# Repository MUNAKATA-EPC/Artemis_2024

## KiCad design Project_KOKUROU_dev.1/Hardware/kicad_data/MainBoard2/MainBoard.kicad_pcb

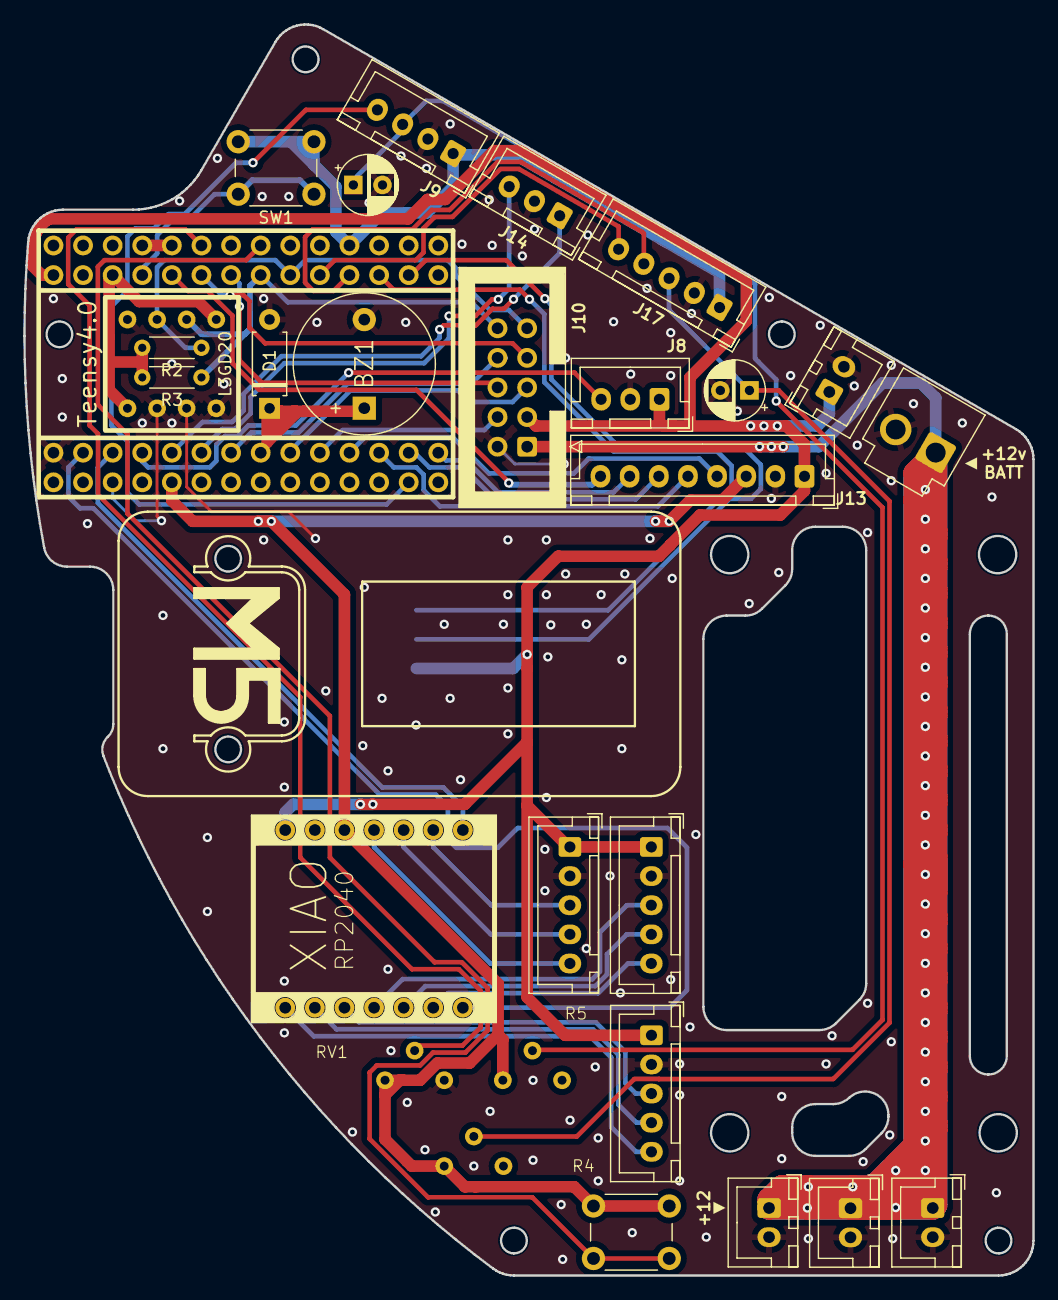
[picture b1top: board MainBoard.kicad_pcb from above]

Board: 2 copper layers, 86.6 x 107.3 mm, 29 parts (1 on the bottom side), 41 nets.

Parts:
BZ1: Buzzer; Buzzer_12x9.5RM7.6
C1, C2: C; CP_Radial_D5.0mm_P2.50mm
D1: D; D_A-405_P7.62mm_Horizontal
J1, J2, J3, J17: Conn_01x05_Socket; JST_XH_B5B-XH-A_1x05_P2.50mm_Vertical
J4, J5, J6, J12: Conn_01x02_Socket; JST_XH_B2B-XH-A_1x02_P2.50mm_Vertical
J7: Conn_01x04_Socket; JST_XH_S4B-XH-A_1x04_P2.50mm_Horizontal
J8, J14: Conn_01x03_Socket; JST_XH_B3B-XH-A_1x03_P2.50mm_Vertical
J9: Conn_01x04_Socket; JST_XH_B4B-XH-A_1x04_P2.50mm_Vertical
J10: Conn_01x10_Socket; IDC-Header_2x05_P2.54mm_Vertical
J11: Conn_01x02_Socket; JST_VH_B2P-VH-B_1x02_P3.96mm_Vertical
J13: Conn_01x08_Socket; JST_XH_B8B-XH-A_1x08_P2.50mm_Vertical
R2, R3: R; R_Axial_DIN0204_L3.6mm_D1.6mm_P5.08mm_Horizontal
R4, R5: R_Trim; 可変抵抗
RV1: R_Potentiometer_Trim_US; 可変抵抗
SW1, SW2: SW_Push; SW_PUSH_6mm_H5mm
U1: Teensy4.0; Teensy_Brakeout
U2: SeeeduinoXIAO; seeeduinoXIAO
U3: L3GD20H_Module_KiCad6.0

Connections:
+3.3V: J9.1, J13.3, J17.1, R2.2, R3.2, R4.1, R5.1, RV1.1, SW1.2, SW2.2, U1.31 (3V3), U2.12 (3V3), U3.1 (VCC), U3.8 (CS)
+5V: J1.1, J2.1, J3.1, J7.2, J8.1, J10.3, J12.1, J13.1, U1.33 (VIN), U2.14 (5V)
+12V: J4.1, J5.1, J6.1, J10.1, J11.1
BLDC_PWM: J8.3, U1.4 (2_OUT2)
BTN_EX: SW2.1, U1.37 (26_A12_MOSI1)
BTN_Left: J13.5, U1.12 (10_CS_MQSR)
BTN_Right: J13.7, U1.14 (12_MISO_MQSL)
BTN_Run: J13.6, U1.13 (11_MOSI_CTX1)
Buzzer: BZ1.1 (-), D1.1 (K), U1.8 (6_OUT1D)
CAM_RX: J10.7, U1.28 (21_A7_RX5_BCLK1)
CAM_TX: J10.6, U1.27 (20_A6_TX5_LRCLK1)
FET1_Digital: J14.1, U1.5 (3_LRCLK2)
FET2_Digital: J14.3, U1.6 (4_BCLK2)
GND: BZ1.2 (+), C1.2, C2.2, D1.2 (A), J1.2, J2.2, J3.2, J4.2, J5.2, J6.2, J7.1, J8.2, J9.2, J10.2, J11.2, J12.2, J13.2, J14.2, J17.2, RV1.3, U1.1 (GND), U2.13 (GND), U3.4 (SA0), U3.5 (GND), U3.6 (INT1), U3.7 (INT2)
IMU_RX: J7.4, U1.22 (15_A1_RX3_SPDIF_IN)
IMU_TX: J7.3, U1.21 (14_A0_TX3_SPDIF_OUT)
IND_PWM: J13.8, U1.29 (22_A8_CTX1)
IR_RX: J10.5, U1.9 (7_RX2_OUT1A)
IR_TX: J10.4, U1.10 (8_TX2_IN1)
L3GD_RST: SW1.1, U1.30 (23_A9_CRX1_MCLK1)
L3GD_SCL: J10.10, R3.1, U1.26 (19_A5_SCL0), U3.2 (SCL)
L3GD_SDA: J10.9, R2.1, U1.25 (18_A4_SDA0), U3.3 (SDA)
L3GD_Trim: RV1.2, U1.38 (27_A13_SCK1)
LINE_RX: J17.4, U1.23 (16_A2_RX4_SCL1)
LINE_TX: J17.5, U1.24 (17_A3_TX4_SDA1)
MD1_INA: J1.3, U2.3 (PA10_A2_D2)
MD1_INB: J1.4, U2.2 (PA4_A1_D1)
MD1_PWM: J1.5, U2.1 (PA02_A0_D0)
MD2_INA: J2.3, U2.4 (PA11_A3_D3)
MD2_INB: J2.4, U2.5 (PA8_A4_D4_SDA)
MD2_PWM: J2.5, U2.6 (PA9_A5_D5_SCL)
MD3_INA: J3.3, U2.9 (PA7_A8_D8_SCK)
MD3_INB: J3.4, U2.10 (PA5_A9_D9_MISO)
MD3_PWM: J3.5, U2.11 (PA6_A10_D10_MOSI)
MD_RX: U1.2 (0_RX1_CRX2_CS1), U2.7 (PB08_A6_D6_TX)
MD_TX: U1.3 (1_TX1_CTX2_MISO1), U2.8 (PB09_A7_D7_RX)
NeoPixel_PWM: J10.8, U1.7 (5_IN2)
unnamed: C2.1, J9.3, R5.2
unnamed: C1.1, J17.3, R4.2
SWT_START: J13.4, U1.11 (9_OUT1C)
Touch: J9.4, U1.41 (30_CRX3)

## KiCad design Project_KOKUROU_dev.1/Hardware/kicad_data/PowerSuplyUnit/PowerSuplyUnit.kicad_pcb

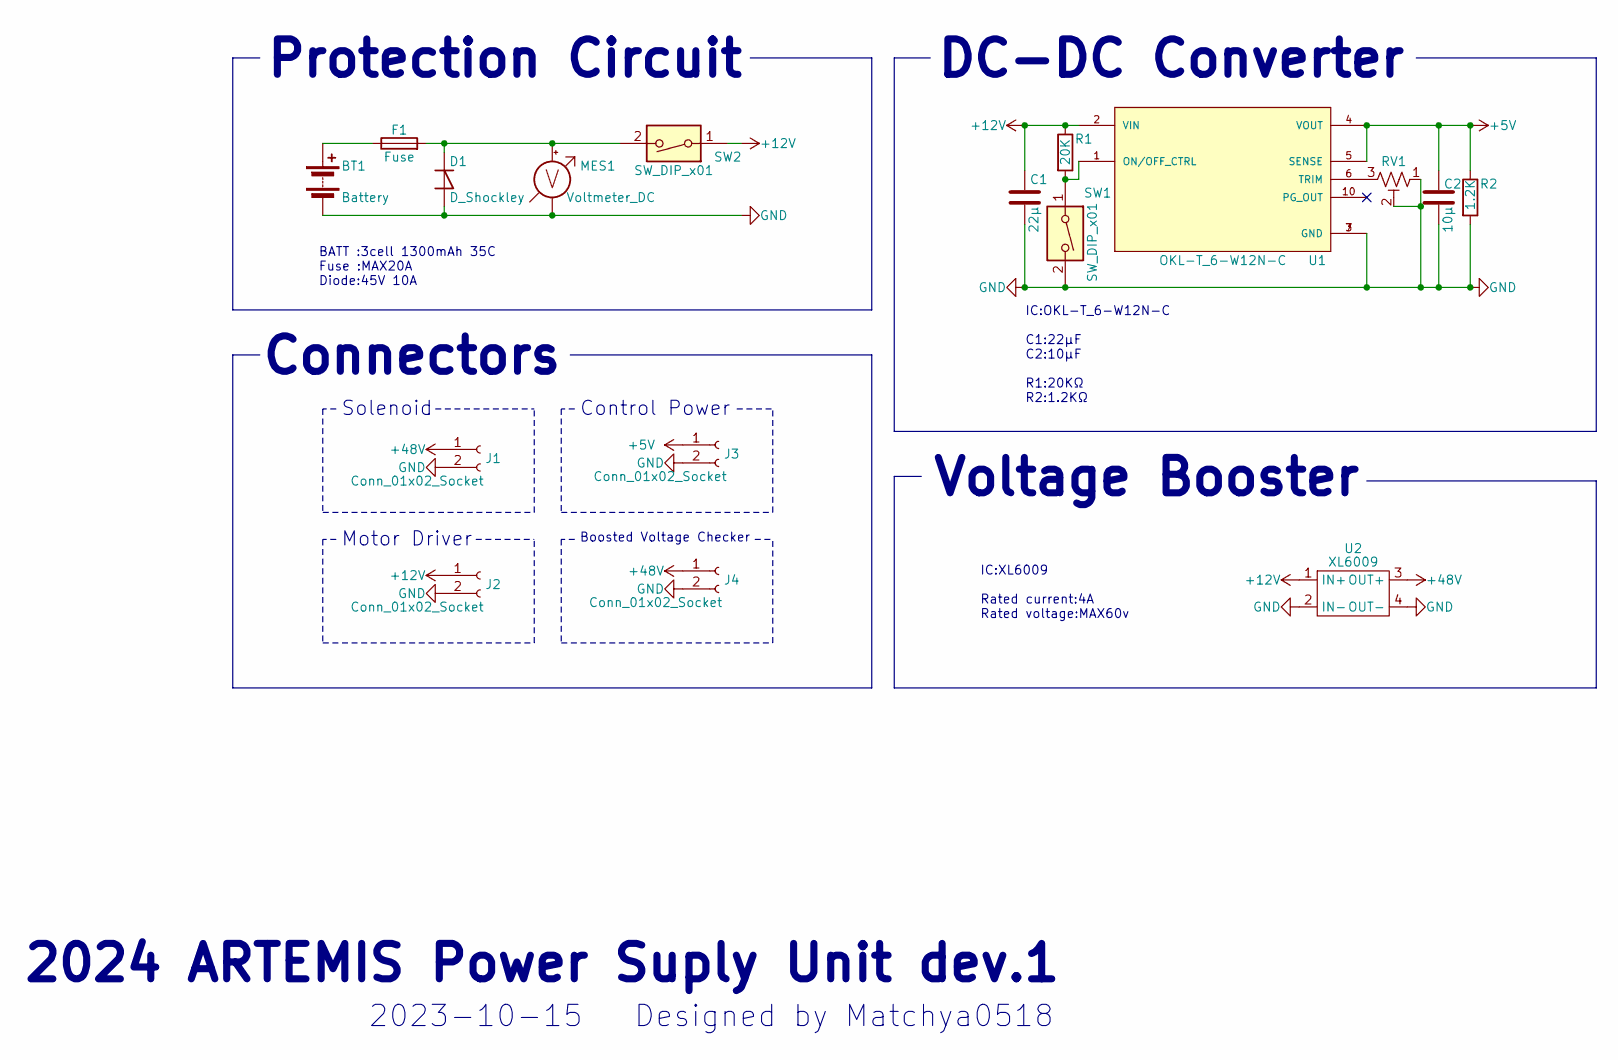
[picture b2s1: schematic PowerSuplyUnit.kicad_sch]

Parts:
BT1: Battery; JST_VH_B2P-VH_1x02_P3.96mm_Vertical
C1: 22μ; C_Disc_D4.7mm_W2.5mm_P5.00mm
C2: 10μ; C_Disc_D4.7mm_W2.5mm_P5.00mm
D1: D_Shockley; D_DO-27_P12.70mm_Horizontal
F1: Fuse; fuse_socket
J1, J3, J4: Conn_01x02_Socket; JST_XH_B2B-XH-A_1x02_P2.50mm_Vertical
J2: Conn_01x02_Socket; JST_VH_B2P-VH-B_1x02_P3.96mm_Vertical
MES1: Voltmeter_DC; voltage_counter
R1: 20K; R_Axial_DIN0204_L3.6mm_D1.6mm_P5.08mm_Horizontal
R2: 1.2K; R_Axial_DIN0204_L3.6mm_D1.6mm_P5.08mm_Horizontal
RV1: R_Potentiometer_Trim_US; Potentiometer_Bourns_3296W_Vertical
SW1: SW_DIP_x01; SW_S
SW2: SW_DIP_x01; DS-850k
U1: OKL-T_6-W12N-C; DCDC-murata-6A
U2: XL6009

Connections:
+5V: C2.1, J3.1, R2.1, U1.4 (VOUT), U1.5 (SENSE)
+12V: C1.1, J2.1, R1.1, SW2.1, U1.2 (VIN), U2.1 (IN+); also elsewhere on the board
+48V: J1.1, J4.1, U2.3 (OUT+)
GND: BT1.2 (-), C1.2, C2.2, D1.2 (A), J1.2, J2.2, J3.2, J4.2, MES1.1 (-), R2.2, RV1.1, RV1.2, SW1.2, U1.3 (GND), U1.7 (GND), U2.2 (IN-), U2.4 (OUT-); also elsewhere on the board
unnamed: BT1.1 (+), F1.1
unnamed: D1.1 (K), F1.2, MES1.2 (+), SW2.2
unnamed: R1.2, SW1.1, U1.1 (ON/OFF_CTRL)
unnamed: RV1.3, U1.6 (TRIM)

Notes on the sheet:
Control Power
BATT :3cell 1300mAh 35C Fuse :MAX20A Diode:45V 10A
Protection Circuit
Voltage Booster
IC:OKL-T_6-W12N-C C1:22μF C2:10μF R1:20KΩ R2:1.2KΩ
DC-DC Converter
IC:XL6009 Rated current:4A Rated voltage:MAX60v
Boosted Voltage Checker
Designed by Matchya0518
2024 ARTEMIS Power Suply Unit dev.1
Connectors
Solenoid
Motor Driver
2023-10-15

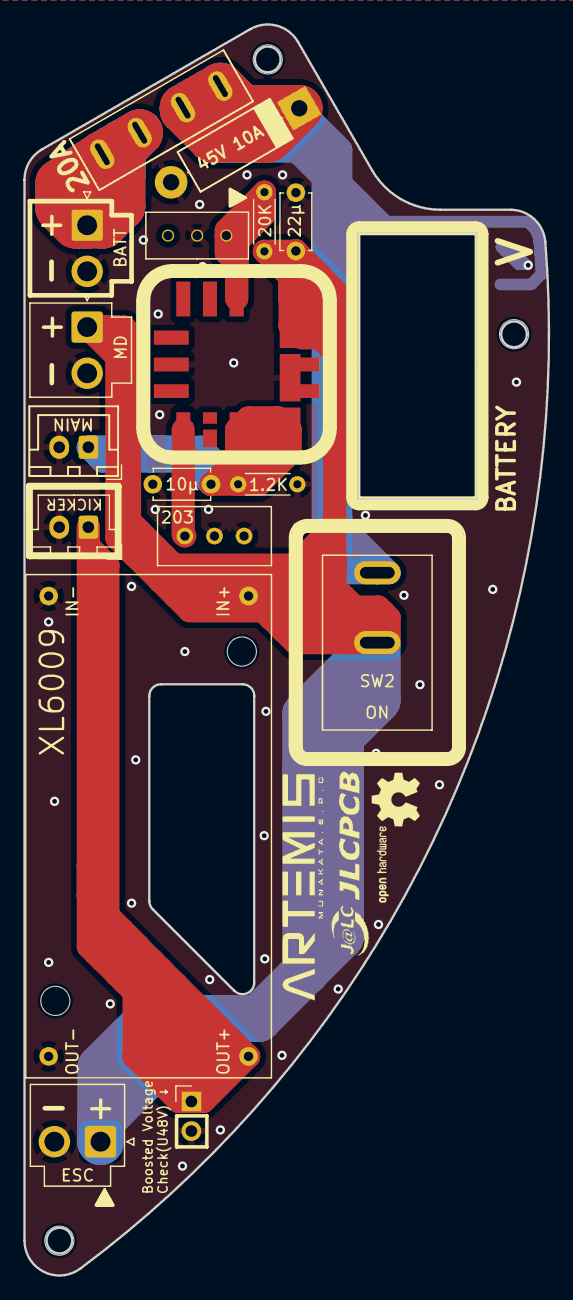
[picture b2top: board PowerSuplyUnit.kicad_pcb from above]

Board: 2 copper layers, 45.0 x 107.3 mm, 18 parts (0 on the bottom side), 8 nets.

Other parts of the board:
J2#2: Conn_01x02_Socket; JST_VH_B2P-VH-B_1x02_P3.96mm_Vertical

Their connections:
+12V: J2#2.1; also elsewhere on the board
GND: J2#2.2; also elsewhere on the board

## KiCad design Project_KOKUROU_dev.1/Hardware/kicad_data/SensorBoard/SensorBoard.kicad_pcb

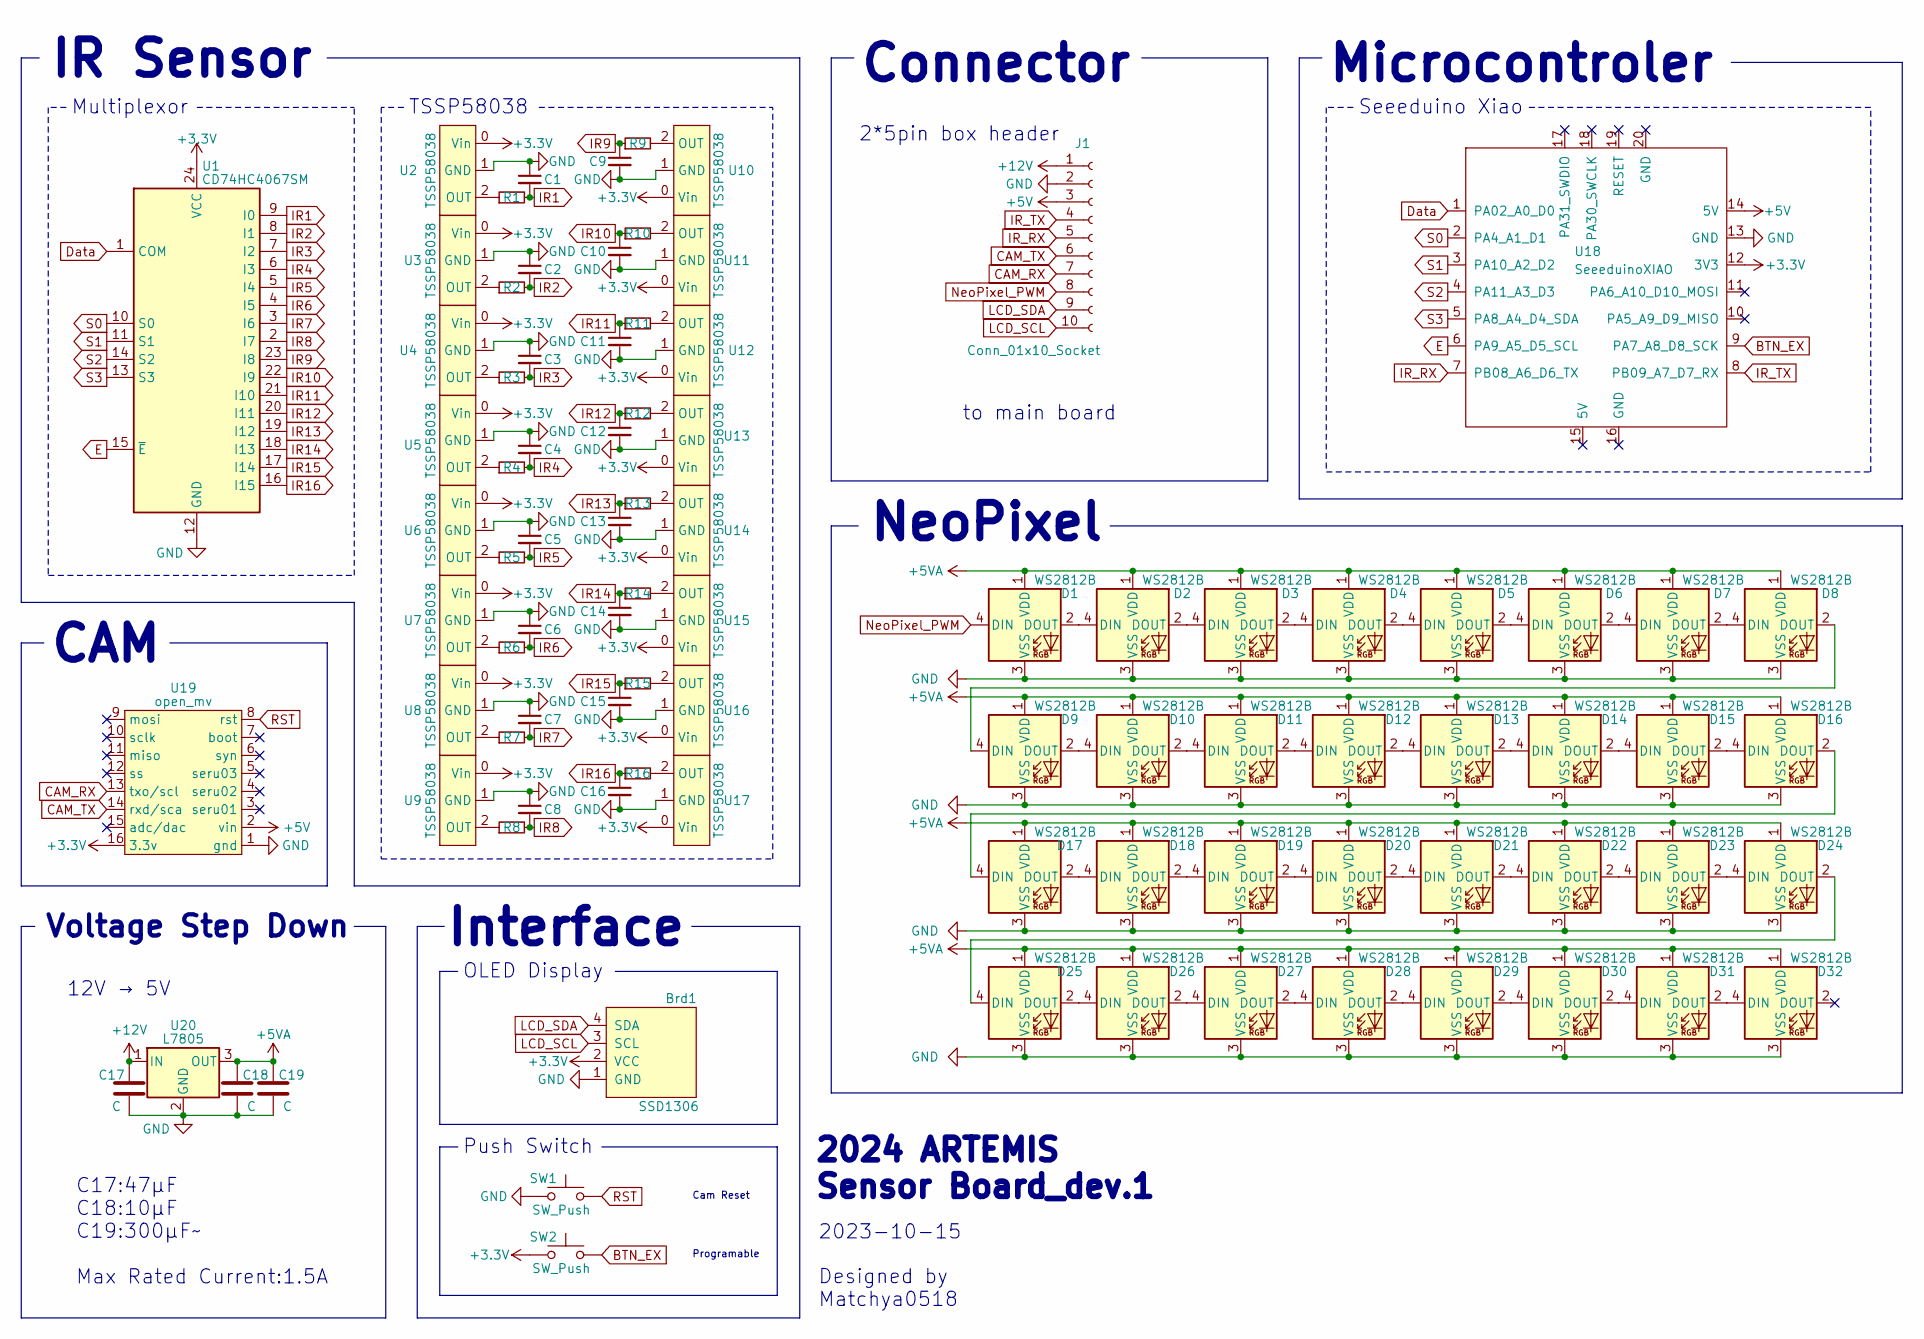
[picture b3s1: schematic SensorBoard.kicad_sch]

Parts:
Brd1: SSD1306; 128x64OLED
C1, C2, C3, C4, C5, C6, C7, C8, C9, C10, C11, C12, C13, C14, C15, C16: C_Small; C_0402_1005Metric
C17, C19: C; CP_Elec_5x5.4
C18: C; C_0402_1005Metric
D1, D2, D3, D4, D5, D6, D7, D8, D9, D10, D11, D12, D13, D14, D15, D16, D17, D18, D19, D20, D21, D22, D23, D24, D25, D26, D27, D28, D29, D30, D31, D32: WS2812B; LED_WS2812B-Mini_3.5x3.5mm
J1: Conn_01x10_Socket; IDC-Header_2x05_P2.54mm_Vertical
R1, R2, R3, R4, R5, R6, R7, R8, R9, R10, R11, R12, R13, R14, R15, R16: R_Small; C_0402_1005Metric
SW1, SW2: SW_Push; SW_PUSH_6mm_H5mm
U1: CD74HC4067SM; SSOP-24_5.3x8.2mm_P0.65mm
U2, U3, U4, U5, U6, U7, U8, U9, U10, U11, U12, U13, U14, U15, U16, U17: TSSP58038
U18: SeeeduinoXIAO; seeeduinoXIAO
U19: open_mv; OpenMV
U20: L7805; 3端子レギュレータ

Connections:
+3.3V: Brd1.2 (VCC), SW2.1, U1.24 (VCC), U2.0 (Vin), U3.0 (Vin), U4.0 (Vin), U5.0 (Vin), U6.0 (Vin), U7.0 (Vin), U8.0 (Vin), U9.0 (Vin), U10.0 (Vin), U11.0 (Vin), U12.0 (Vin), U13.0 (Vin), U14.0 (Vin), U15.0 (Vin), U16.0 (Vin), U17.0 (Vin), U18.12 (3V3), U19.16 (3.3v)
+5V: J1.3, U18.14 (5V), U19.2 (vin)
+5VA: C18.1, C19.1, D1.1 (VDD), D2.1 (VDD), D3.1 (VDD), D4.1 (VDD), D5.1 (VDD), D6.1 (VDD), D7.1 (VDD), D8.1 (VDD), D9.1 (VDD), D10.1 (VDD), D11.1 (VDD), D12.1 (VDD), D13.1 (VDD), D14.1 (VDD), D15.1 (VDD), D16.1 (VDD), D17.1 (VDD), D18.1 (VDD), D19.1 (VDD), D20.1 (VDD), D21.1 (VDD), D22.1 (VDD), D23.1 (VDD), D24.1 (VDD), D25.1 (VDD), D26.1 (VDD), D27.1 (VDD), D28.1 (VDD), D29.1 (VDD), D30.1 (VDD), D31.1 (VDD), D32.1 (VDD), U20.3 (OUT)
+12V: C17.1, J1.1, U20.1 (IN)
BTN_EX: SW2.2, U18.9 (PA7_A8_D8_SCK)
CAM_RX: J1.7, U19.13 (txo/scl)
CAM_TX: J1.6, U19.14 (rxd/sca)
Data: U1.1 (COM), U18.1 (PA02_A0_D0)
E: U1.15 (~E), U18.6 (PA9_A5_D5_SCL)
GND: Brd1.1 (GND), C1.1, C2.1, C3.1, C4.1, C5.1, C6.1, C7.1, C8.1, C9.2, C10.2, C11.2, C12.2, C13.2, C14.2, C15.2, C16.2, C17.2, C18.2, C19.2, D1.3 (VSS), D2.3 (VSS), D3.3 (VSS), D4.3 (VSS), D5.3 (VSS), D6.3 (VSS), D7.3 (VSS), D8.3 (VSS), D9.3 (VSS), D10.3 (VSS), D11.3 (VSS), D12.3 (VSS), D13.3 (VSS), D14.3 (VSS), D15.3 (VSS), D16.3 (VSS), D17.3 (VSS), D18.3 (VSS), D19.3 (VSS), D20.3 (VSS), D21.3 (VSS), D22.3 (VSS), D23.3 (VSS), D24.3 (VSS), D25.3 (VSS), D26.3 (VSS), D27.3 (VSS), D28.3 (VSS), D29.3 (VSS), D30.3 (VSS), D31.3 (VSS), D32.3 (VSS), J1.2, SW1.1, U1.12 (GND), U2.1 (GND), U3.1 (GND), U4.1 (GND), U5.1 (GND), U6.1 (GND), U7.1 (GND), U8.1 (GND), U9.1 (GND), U10.1 (GND), U11.1 (GND), U12.1 (GND), U13.1 (GND), U14.1 (GND), U15.1 (GND), U16.1 (GND), U17.1 (GND), U18.13 (GND), U19.1 (gnd), U20.2 (GND)
IR1: C1.2, R1.2, U1.9 (I0)
IR2: C2.2, R2.2, U1.8 (I1)
IR3: C3.2, R3.2, U1.7 (I2)
IR4: C4.2, R4.2, U1.6 (I3)
IR5: C5.2, R5.2, U1.5 (I4)
IR6: C6.2, R6.2, U1.4 (I5)
IR7: C7.2, R7.2, U1.3 (I6)
IR8: C8.2, R8.2, U1.2 (I7)
IR9: C9.1, R9.1, U1.23 (I8)
IR10: C10.1, R10.1, U1.22 (I9)
IR11: C11.1, R11.1, U1.21 (I10)
IR12: C12.1, R12.1, U1.20 (I11)
IR13: C13.1, R13.1, U1.19 (I12)
IR14: C14.1, R14.1, U1.18 (I13)
IR15: C15.1, R15.1, U1.17 (I14)
IR16: C16.1, R16.1, U1.16 (I15)
IR_RX: J1.5, U18.7 (PB08_A6_D6_TX)
IR_TX: J1.4, U18.8 (PB09_A7_D7_RX)
LCD_SCL: Brd1.3 (SCL), J1.10
LCD_SDA: Brd1.4 (SDA), J1.9
NeoPixel_PWM: D1.4 (DIN), J1.8
unnamed: D1.2 (DOUT), D2.4 (DIN)
unnamed: D2.2 (DOUT), D3.4 (DIN)
unnamed: D3.2 (DOUT), D4.4 (DIN)
unnamed: D4.2 (DOUT), D5.4 (DIN)
unnamed: D5.2 (DOUT), D6.4 (DIN)
unnamed: D6.2 (DOUT), D7.4 (DIN)
unnamed: D7.2 (DOUT), D8.4 (DIN)
unnamed: D8.2 (DOUT), D9.4 (DIN)
unnamed: D9.2 (DOUT), D10.4 (DIN)
unnamed: D10.2 (DOUT), D11.4 (DIN)
unnamed: D11.2 (DOUT), D12.4 (DIN)
unnamed: D12.2 (DOUT), D13.4 (DIN)
unnamed: D13.2 (DOUT), D14.4 (DIN)
unnamed: D14.2 (DOUT), D15.4 (DIN)
unnamed: D15.2 (DOUT), D16.4 (DIN)
unnamed: D16.2 (DOUT), D17.4 (DIN)
unnamed: D17.2 (DOUT), D18.4 (DIN)
unnamed: D18.2 (DOUT), D19.4 (DIN)
unnamed: D19.2 (DOUT), D20.4 (DIN)
unnamed: D20.2 (DOUT), D21.4 (DIN)
unnamed: D21.2 (DOUT), D22.4 (DIN)
unnamed: D22.2 (DOUT), D23.4 (DIN)
unnamed: D23.2 (DOUT), D24.4 (DIN)
unnamed: D24.2 (DOUT), D25.4 (DIN)
unnamed: D25.2 (DOUT), D26.4 (DIN)
unnamed: D26.2 (DOUT), D27.4 (DIN)
unnamed: D27.2 (DOUT), D28.4 (DIN)
unnamed: D28.2 (DOUT), D29.4 (DIN)
unnamed: D29.2 (DOUT), D30.4 (DIN)
unnamed: D30.2 (DOUT), D31.4 (DIN)
unnamed: D31.2 (DOUT), D32.4 (DIN)
unnamed: R1.1, U2.2 (OUT)
unnamed: R2.1, U3.2 (OUT)
unnamed: R3.1, U4.2 (OUT)
unnamed: R4.1, U5.2 (OUT)
unnamed: R5.1, U6.2 (OUT)
unnamed: R6.1, U7.2 (OUT)
unnamed: R7.1, U8.2 (OUT)
unnamed: R8.1, U9.2 (OUT)
unnamed: R9.2, U10.2 (OUT)
unnamed: R10.2, U11.2 (OUT)
unnamed: R11.2, U12.2 (OUT)
unnamed: R12.2, U13.2 (OUT)
unnamed: R13.2, U14.2 (OUT)
unnamed: R14.2, U15.2 (OUT)
unnamed: R15.2, U16.2 (OUT)
unnamed: R16.2, U17.2 (OUT)
RST: SW1.2, U19.8 (rst)
S0: U1.10 (S0), U18.2 (PA4_A1_D1)
S1: U1.11 (S1), U18.3 (PA10_A2_D2)
S2: U1.14 (S2), U18.4 (PA11_A3_D3)
S3: U1.13 (S3), U18.5 (PA8_A4_D4_SDA)

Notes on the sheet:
Seeeduino Xiao
IR Sensor
2024 ARTEMIS Sensor Board_dev.1
Push Switch
TSSP58038
to main board
Programable
Voltage Step Down
C17:47μF C18:10μF C19:300μF~ Max Rated Current:1.5A
CAM
12V → 5V
Designed by Matchya0518
2023-10-15
Microcontroler
NeoPixel
Interface
Cam Reset
Multiplexor
OLED Display
Connector
2*5pin box header

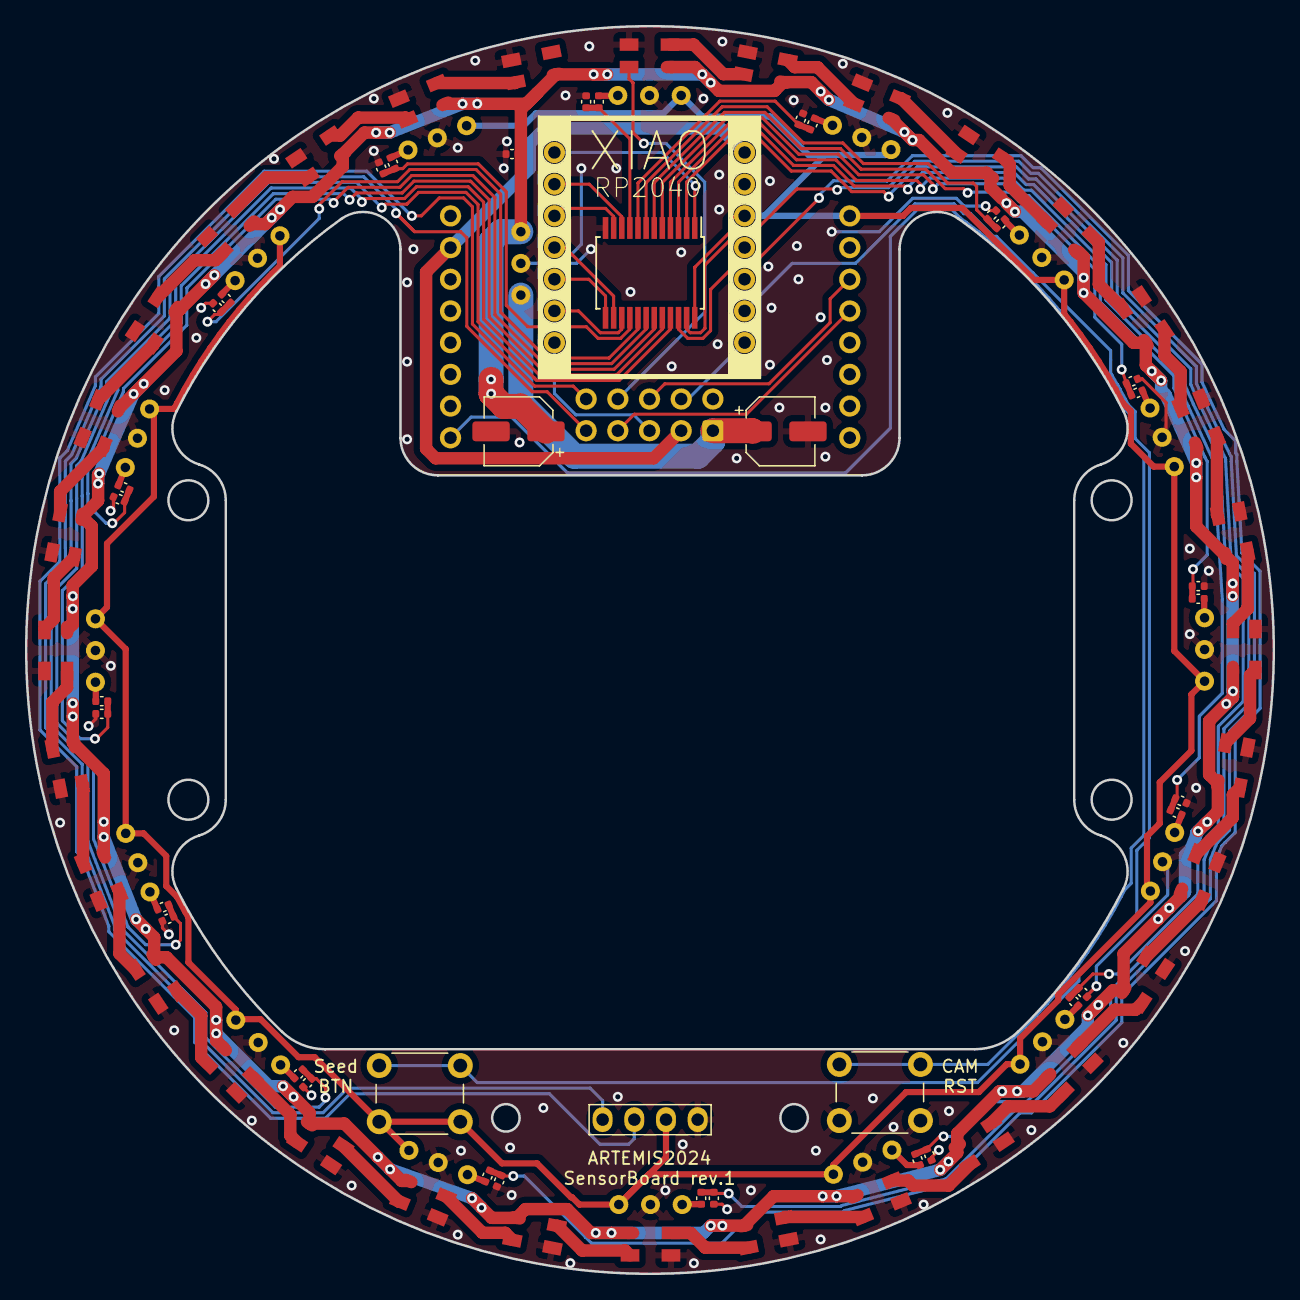
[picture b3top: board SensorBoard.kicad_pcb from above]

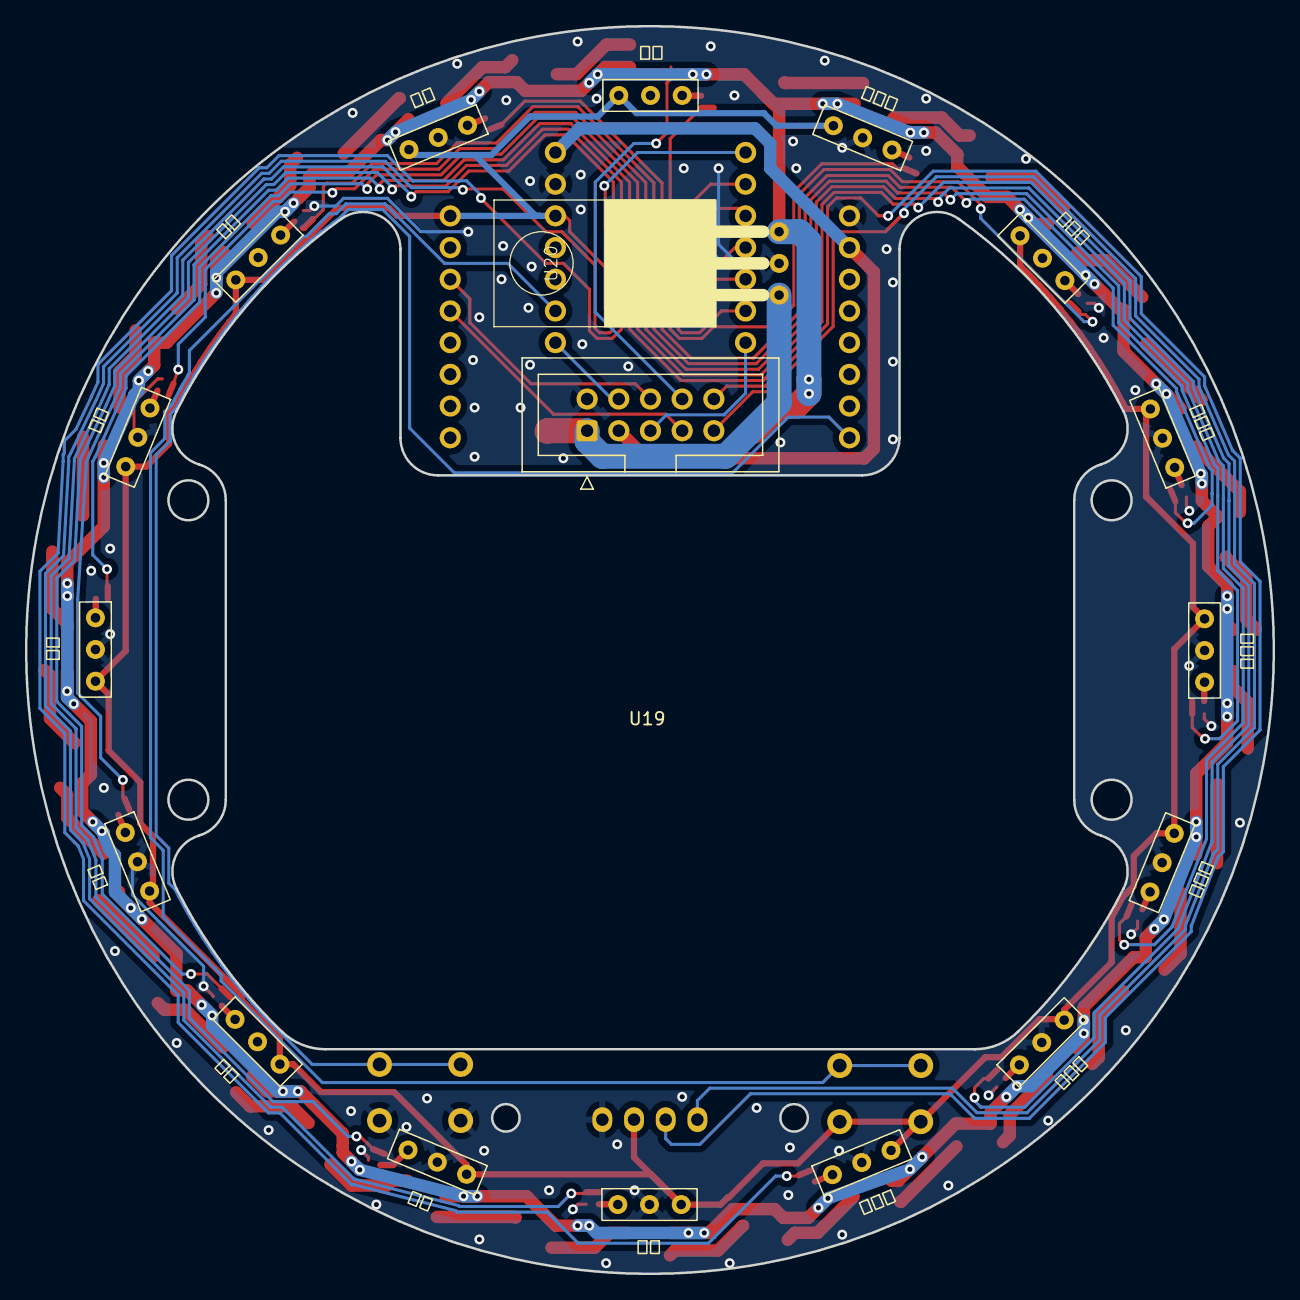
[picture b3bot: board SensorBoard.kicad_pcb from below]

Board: 2 copper layers, 100.0 x 100.0 mm, 91 parts (19 on the bottom side), 83 nets.

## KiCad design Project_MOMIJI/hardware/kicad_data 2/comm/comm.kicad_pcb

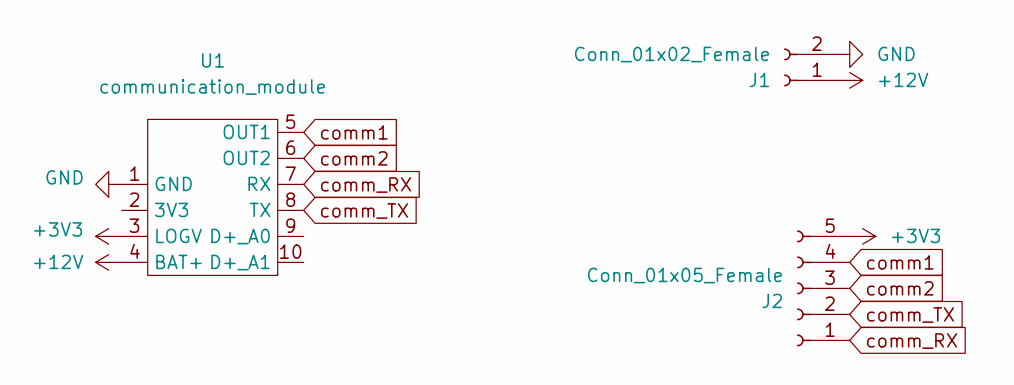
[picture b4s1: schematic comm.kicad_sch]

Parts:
J1: Conn_01x02_Female; JST_XH_S2B-XH-A_1x02_P2.50mm_Horizontal
J2: Conn_01x05_Female; JST_XH_S5B-XH-A_1x05_P2.50mm_Horizontal
U1: communication_module; comm

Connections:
+3V3: J2.5, U1.3 (LOGV)
+12V: J1.1, U1.4 (BAT+)
GND: J1.2, U1.1 (GND)
comm1: J2.4, U1.5 (OUT1)
comm2: J2.3, U1.6 (OUT2)
comm_RX: J2.1, U1.7 (RX)
comm_TX: J2.2, U1.8 (TX)

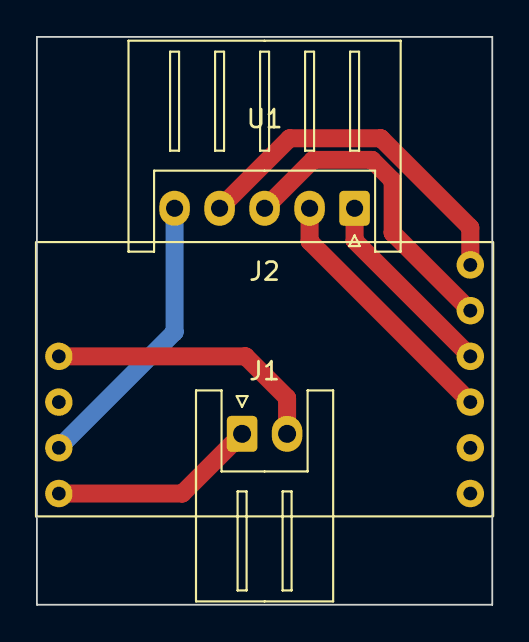
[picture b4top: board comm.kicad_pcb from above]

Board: 2 copper layers, 25.3 x 31.5 mm, 3 parts (0 on the bottom side), 7 nets.

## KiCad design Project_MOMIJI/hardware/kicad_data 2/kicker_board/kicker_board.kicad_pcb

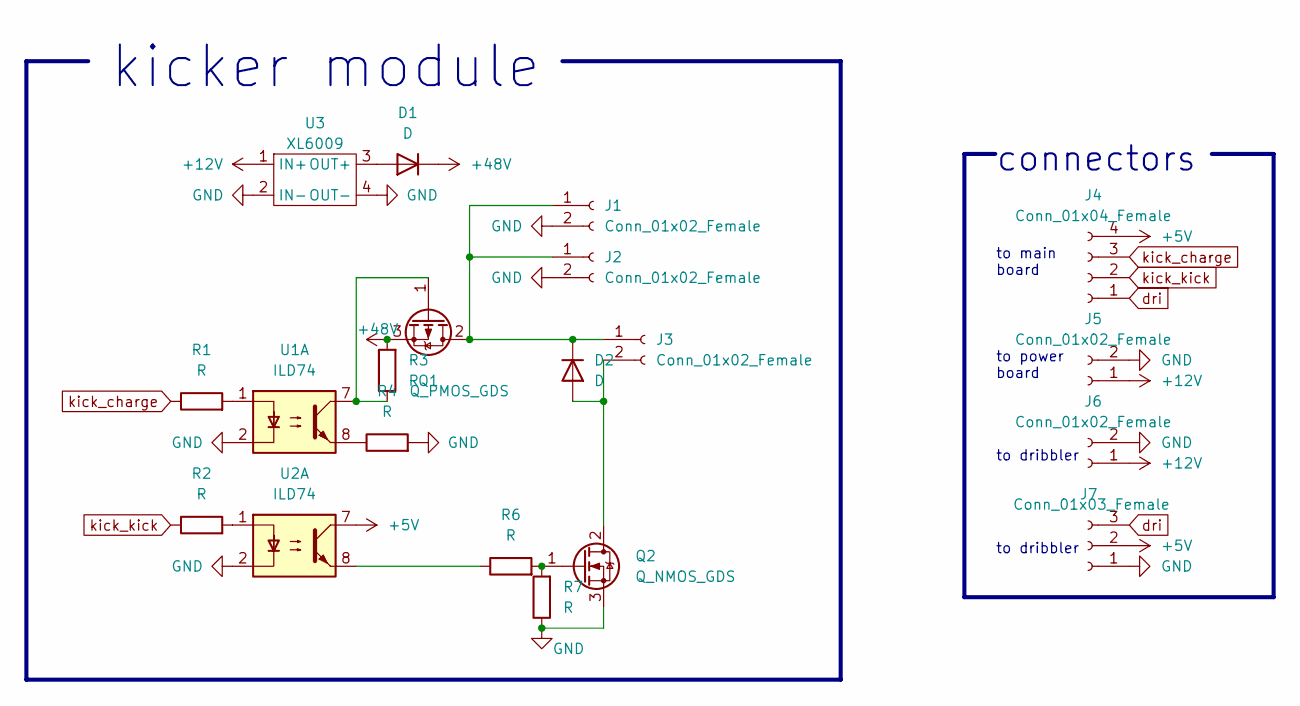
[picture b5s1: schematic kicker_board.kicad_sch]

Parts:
D1, D2: D; D_5W_P12.70mm_Horizontal
J1, J2, J3, J5, J6: Conn_01x02_Female; JST_XH_B2B-XH-A_1x02_P2.50mm_Vertical
J4: Conn_01x04_Female; JST_XH_B4B-XH-A_1x04_P2.50mm_Vertical
J7: Conn_01x03_Female; JST_XH_B3B-XH-A_1x03_P2.50mm_Vertical
Q1: Q_PMOS_GDS; Pch MOSFET
Q2: Q_NMOS_GDS; Pch MOSFET
R1, R2, R3, R4, R6, R7: R; R_Axial_DIN0207_L6.3mm_D2.5mm_P7.62mm_Horizontal
U1, U2: ILD74; フォトカプラー
U3: XL6009

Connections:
+5V: J4.4, J7.2, U2.7
+12V: J5.1, J6.1, U3.1 (IN+)
+48V: D1.1 (K), Q1.3 (S), R3.2
GND: J1.2, J2.2, J5.2, J6.2, J7.1, Q2.3 (S), R4.2, R7.1, U1.2, U2.2, U3.2 (IN-), U3.4 (OUT-)
unnamed: D1.2 (A), U3.3 (OUT+)
unnamed: D2.1 (K), J1.1, J2.1, J3.1, Q1.2 (D)
unnamed: D2.2 (A), J3.2, Q2.2 (D)
unnamed: Q1.1 (G), R3.1, U1.7
unnamed: Q2.1 (G), R6.2, R7.2
unnamed: R1.2, U1.1
unnamed: R2.2, U2.1
unnamed: R4.1, U1.8
unnamed: R6.1, U2.8
dri: J4.1, J7.3
kick_charge: J4.3, R1.1
kick_kick: J4.2, R2.1

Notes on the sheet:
to dribbler
kicker module
to main board
connectors
to power board

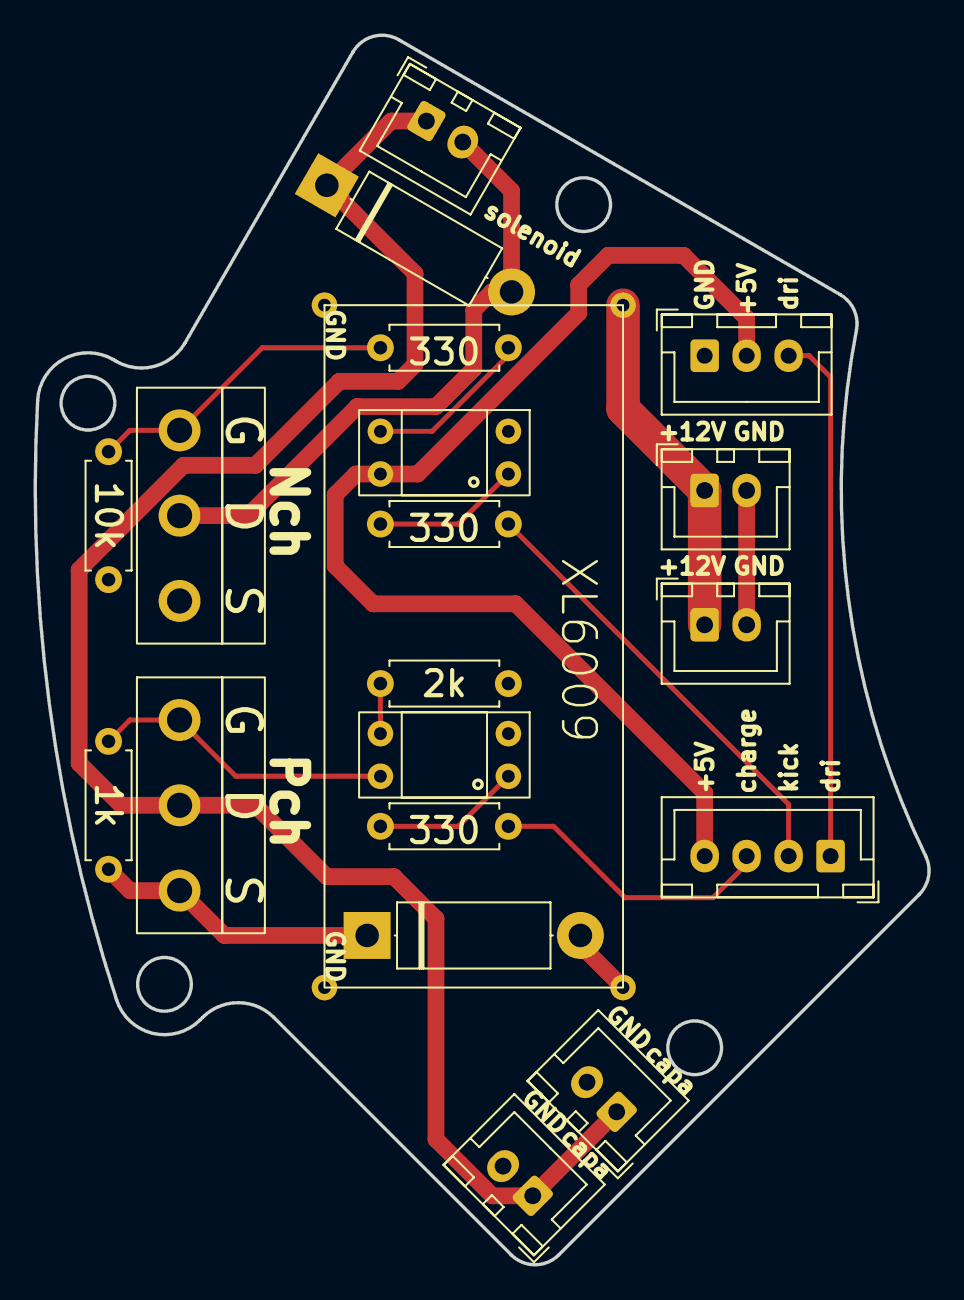
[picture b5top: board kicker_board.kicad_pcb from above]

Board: 2 copper layers, 53.2 x 73.2 mm, 20 parts (0 on the bottom side), 16 nets.
